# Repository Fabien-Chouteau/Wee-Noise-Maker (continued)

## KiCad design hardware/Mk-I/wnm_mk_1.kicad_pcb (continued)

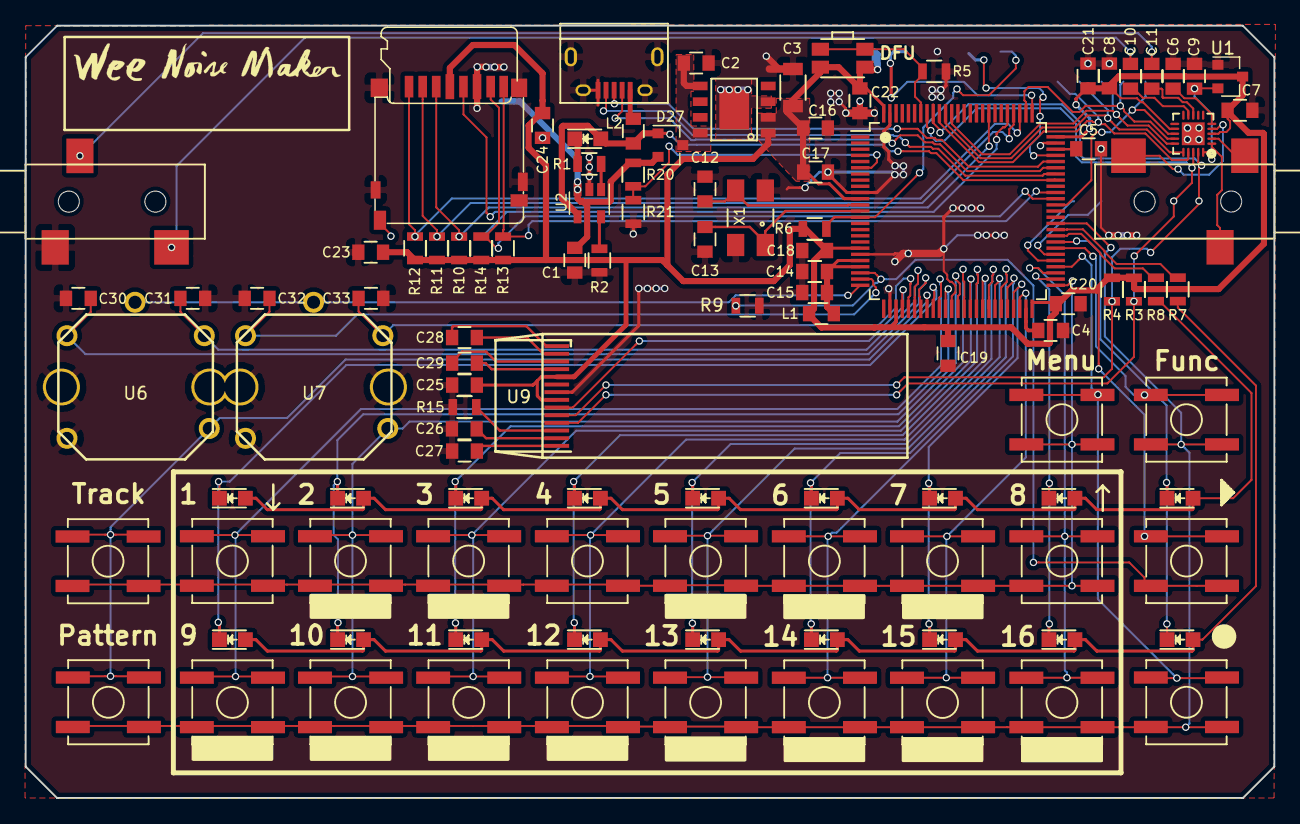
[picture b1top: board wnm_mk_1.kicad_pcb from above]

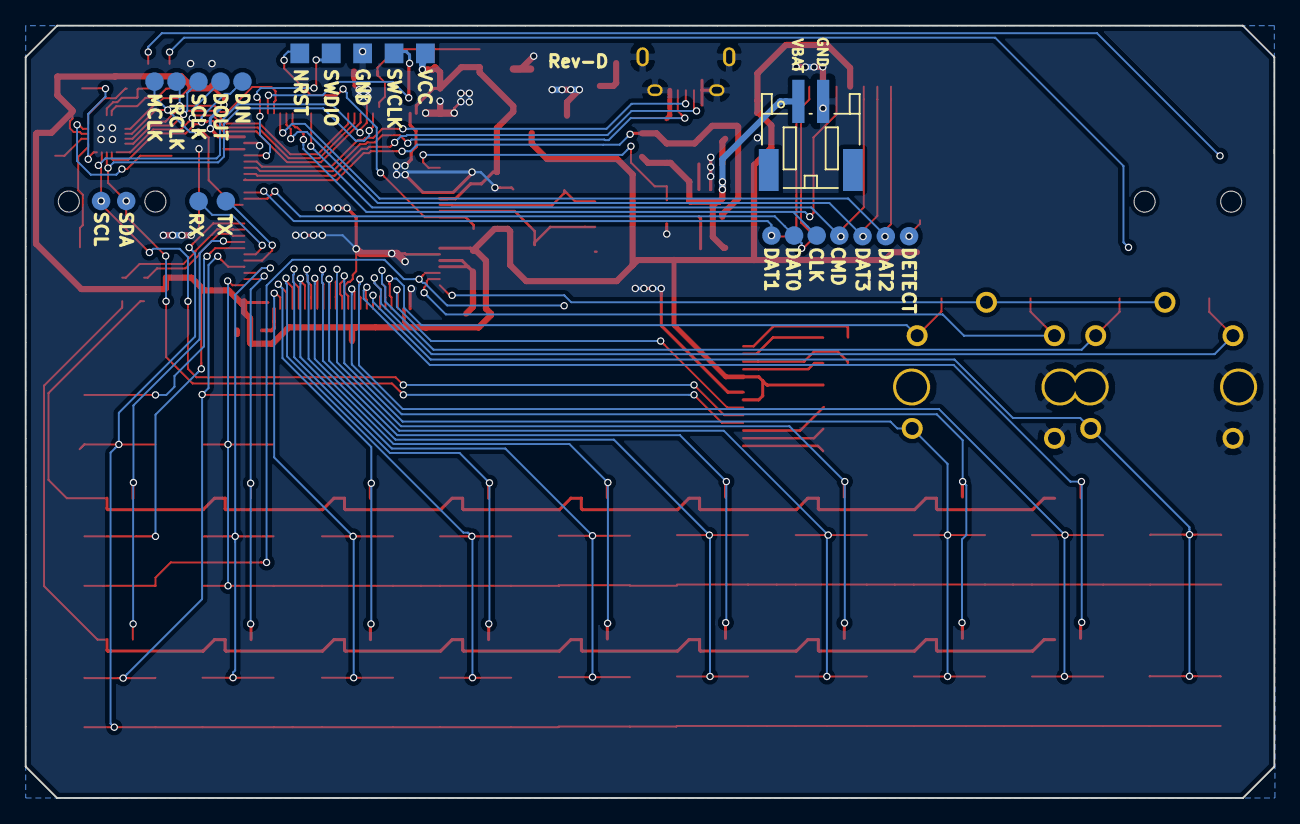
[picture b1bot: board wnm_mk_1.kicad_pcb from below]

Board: 2 copper layers, 100.9 x 62.4 mm, 126 parts (18 on the bottom side), 87 nets.

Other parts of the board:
TP_CMD1: TEST; Measurement_Point_Round-SMD-Pad_Small
TP_DAT2, TP_DAT3: TEST; Measurement_Point_Round-SMD-Pad_Small

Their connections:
SD_CMD: TP_CMD1.1; also elsewhere on the board
SD_DAT2: TP_DAT2.1; also elsewhere on the board
SD_DAT3: TP_DAT3.1; also elsewhere on the board

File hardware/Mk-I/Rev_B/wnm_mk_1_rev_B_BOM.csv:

Id,Designator,Package,Quantity,Designation,Supplier and ref,link
1,G***,logo_hand_line,1,LOGO,,
2,G***,logo_hand_text,1,LOGO,,
3,C2,C_0805,1,4.7uF,08053D475KAT2A,http://www.mouser.fr/ProductDetail/AVX/08053D475KAT2A/?qs=sG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
4,U4,LQFP-100_14x14mm_Pitch0.5mm,1,STM32F407VG,STM32F427VIT6,http://www.mouser.fr/ProductDetail/STMicroelectronics/STM32F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
5,"C26,C27,C1,C25",C_0805,4,10uF,08053D106KAT2A,http://www.mouser.fr/ProductDetail/AVX/08053D106KAT2A/?qs=sG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
6,BT1,PINHEAD1-2,1,BATTERY,,
7,"D24,D25,D1,D2,D3,D4,D5,D6,D7,D8,D9,D10,D11,D12,D13,D14,D15,D16,D17,D18,D20,D21,D22,D23,BAT1",LED_0805,25,LED,150080RS75000,http://www.mouser.fr/Search/ProductDetail.aspx?R=150080RS750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
8,"SW4,SW1,SW7,SW8,SW2,SW3,SW5,SW6,SW9,SW10,SW11,SW12,SW13,SW14,SW15,SW16,Play1,Write1,Play2,SW18,SW19,SW20,SW21,SW22",SW_SPST_B3SL-1002P,24,SW_PUSH,,
9,"C6,C7,C8,C9,C15,C17,C18,C19,C20,C21,C22,C23,C30,C31,C32,C33",C_0805,16,0.1uF,08053C104KAT2A,http://www.mouser.fr/ProductDetail/AVX/08053C104KAT2A/?qs=sG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
10,R1,R_0805,1,1K,CRCW08051K00JNEA,http://www.mouser.fr/ProductDetail/Vishay/CRCW08051K00JNEA/?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
11,U2,SOT-23-5,1,MCP73831,MCP73831T-2ACI/OT,http://www.mouser.fr/ProductDetail/Microchip-Technology/MCP7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
12,CON1,USB_Micro-B,1,USB-MICRO-B,,
13,C3,C_1206,1,47uF,C3216X5R1C476M160AB,http://www.mouser.fr/ProductDetail/TDK/C3216X5R1C476M160AB/?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
14,"R2,R3,R4,R5,R6,R10,R11,R12,R13,R14,R20,R21",R_0805,12,10K,CRCW080510K0JNEA,http://www.mouser.fr/ProductDetail/Vishay/CRCW080510K0JNEA
15,D27,SOT-23,1,DOUBLE_SCH_KCOM_PMEG2005CT,,
16,"C4,C5",C_0805,2,2.2uF,0805YC225KAT2A,http://www.mouser.fr/ProductDetail/AVX/0805YC225KAT2A/?qs=sG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
17,"C10,C11,C14,C28,C29",C_0805,5,1uF,08053C105KAT2A,http://www.mouser.fr/ProductDetail/AVX/08053C105KAT2A/?qs=sG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
18,U5,UQFN-20-1EP_3x3mm_Pitch0.4mm,1,SGTL5000,SGTL5000XNAA3R2,http://www.mouser.fr/ProductDetail/NXP-Freescale/SGTL5000XNA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
19,"C12,C13",C_0805,2,20pF,0805YA200KAT2A,http://www.mouser.fr/ProductDetail/AVX/0805YA200KAT2A/?qs=qV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
20,"C16,C24",C_0805,2,22uF,GRM21BR61C226ME44L,http://www.mouser.fr/ProductDetail/Murata-Electronics/GRM21B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
21,"L1,L2",C_0805,2,15Ohm,CBC2012T4R7M,http://www.mouser.fr/ProductDetail/Taiyo-Yuden/CBC2012T4R7M/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
22,"R7,R8,R9",R_0805,3,330,CRCW0805330RJNEA,http://www.mouser.fr/ProductDetail/Vishay/CRCW0805330RJNEA/?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
23,R15,R_0805,1,68k,CRCW080568K0JNEA,http://www.mouser.fr/ProductDetail/Vishay/CRCW080568K0JNEA/?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
24,"R16,R17,R18,R19",R_0805,4,27K,CRCW080527K0JNEA,http://www.mouser.fr/ProductDetail/Vishay/CRCW080527K0JNEA/?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
25,X1,Crystal_HC49-U_Vertical,1,CRYSTAL,LFXTAL003156Bulk,http://www.mouser.fr/ProductDetail/IQD/LFXTAL003156Bulk/?qs=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
26,"HP_OUT1,LINE_IN1",lumberg_3.5_audio_jack_1503_02,2,3.5_audio_jack,,
27,U8,MOLEX_microSD_47219-2001,1,MOLEX_microSD_47219-2001,,
28,U9,MIDAS_MCOT096016AV_OLED,1,SSD1306,,
29,REF**,MountingHole_4.3mm_M4,1,MountingHole_4.3mm_M4,,
30,DFU_MODE1,SW_SPST_EVQP7A,1,Jumper_NO_Small,EVQ-P7A01P,http://www.mouser.fr/ProductDetail/Panasonic/EVQ-P7A01P/?qs=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
31,"U7,U6",encoder_EC12D,2,encoder_and_switch,EC12D1524403,http://www.mouser.fr/ProductDetail/ALPS/EC12D1524403/?qs=%2f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
32,U3,HTSOP-J8,1,BD33IA5,BD33IA5WEFJ-E2,http://www.mouser.fr/ProductDetail/ROHM-Semiconductor/BD33IA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
33,ext1,Socket_Strip_Straight_1x04,1,CONN_01X04,,
34,U10,STM32_SWD_Connector_SMD,1,STM32_SWD_Connector,,

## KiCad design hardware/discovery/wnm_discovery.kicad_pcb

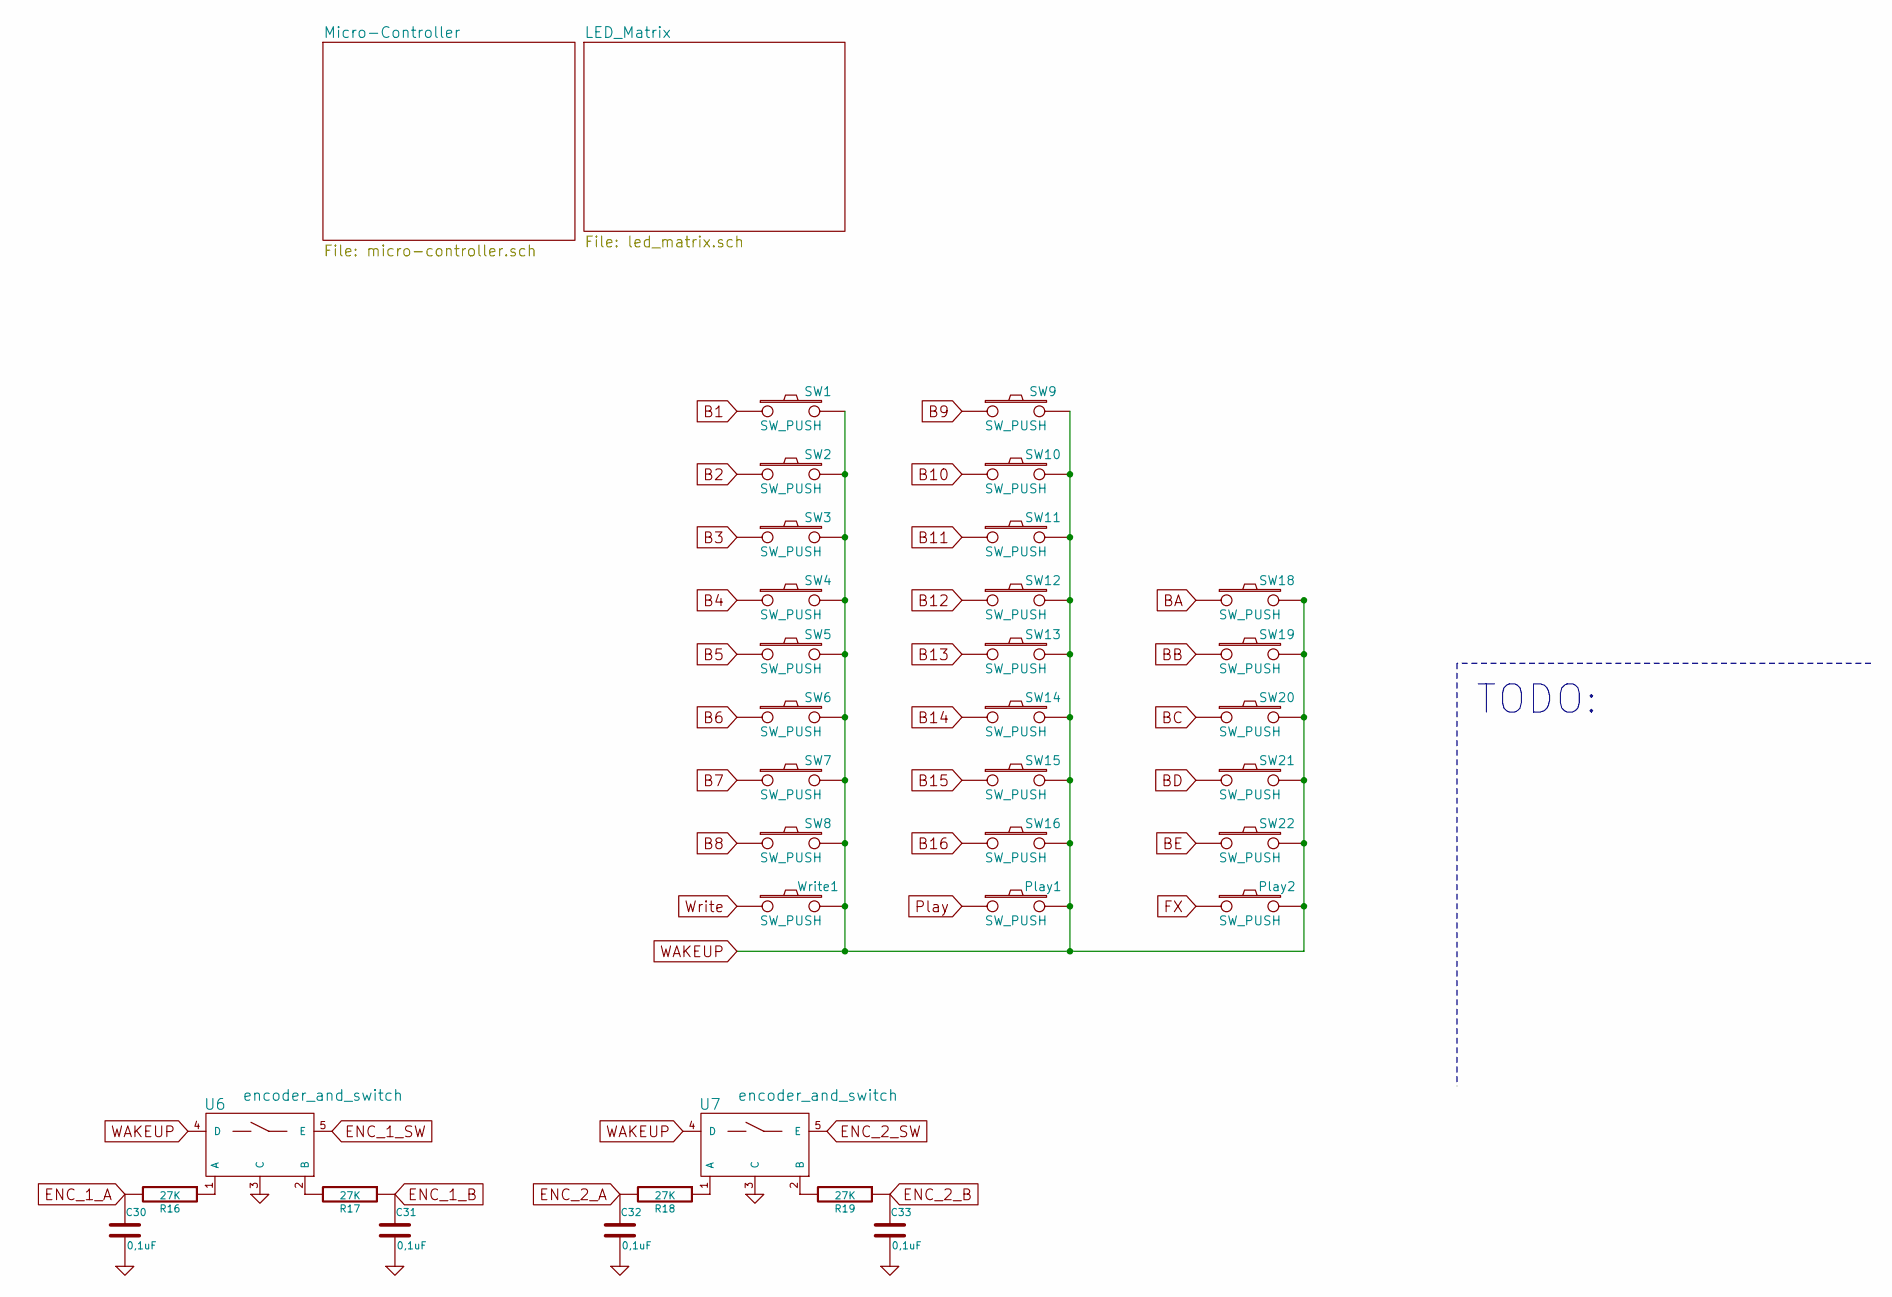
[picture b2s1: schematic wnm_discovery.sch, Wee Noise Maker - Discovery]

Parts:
C30, C31, C32, C33: 0,1uF; C_0805
Play1, Play2: SW_PUSH; SW_SPST_B3SL-1002P
R16, R17, R18, R19: 27K; R_0805
SW1, SW2, SW3, SW4, SW5, SW6, SW7, SW8, SW9, SW10, SW11, SW12, SW13, SW14, SW15, SW16, SW18, SW19, SW20, SW21, SW22: SW_PUSH; SW_SPST_B3SL-1002P
U6, U7: encoder_and_switch; encoder_EC12D
Write1: SW_PUSH; SW_SPST_B3SL-1002P

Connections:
B1: SW1.1; also elsewhere on the board
B2: SW2.1; also elsewhere on the board
B3: SW3.1; also elsewhere on the board
B4: SW4.1; also elsewhere on the board
B5: SW5.1; also elsewhere on the board
B6: SW6.1; also elsewhere on the board
B7: SW7.1; also elsewhere on the board
B8: SW8.1; also elsewhere on the board
B9: SW9.1; also elsewhere on the board
B10: SW10.1; also elsewhere on the board
B11: SW11.1; also elsewhere on the board
B12: SW12.1; also elsewhere on the board
B13: SW13.1; also elsewhere on the board
B14: SW14.1; also elsewhere on the board
B15: SW15.1; also elsewhere on the board
B16: SW16.1; also elsewhere on the board
BA: SW18.1; also elsewhere on the board
BB: SW19.1; also elsewhere on the board
BC: SW20.1; also elsewhere on the board
BD: SW21.1; also elsewhere on the board
BE: SW22.1; also elsewhere on the board
ENC_1_A: C30.1, R16.2; also elsewhere on the board
ENC_1_B: C31.1, R17.1; also elsewhere on the board
ENC_1_SW: U6.5 (E); also elsewhere on the board
ENC_2_A: C32.1, R18.2; also elsewhere on the board
ENC_2_B: C33.1, R19.1; also elsewhere on the board
ENC_2_SW: U7.5 (E); also elsewhere on the board
FX: Play2.1; also elsewhere on the board
GND: C30.2, C31.2, C32.2, C33.2, U6.3 (C), U7.3 (C); also elsewhere on the board
unnamed: R16.1, U6.1 (A)
unnamed: R17.2, U6.2 (B)
unnamed: R18.1, U7.1 (A)
unnamed: R19.2, U7.2 (B)
Play: Play1.1; also elsewhere on the board
WAKEUP: Play1.2, Play2.2, SW1.2, SW2.2, SW3.2, SW4.2, SW5.2, SW6.2, SW7.2, SW8.2, SW9.2, SW10.2, SW11.2, SW12.2, SW13.2, SW14.2, SW15.2, SW16.2, SW18.2, SW19.2, SW20.2, SW21.2, SW22.2, U6.4 (D), U7.4 (D), Write1.2; also elsewhere on the board
Write: Write1.1; also elsewhere on the board

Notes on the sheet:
TODO:

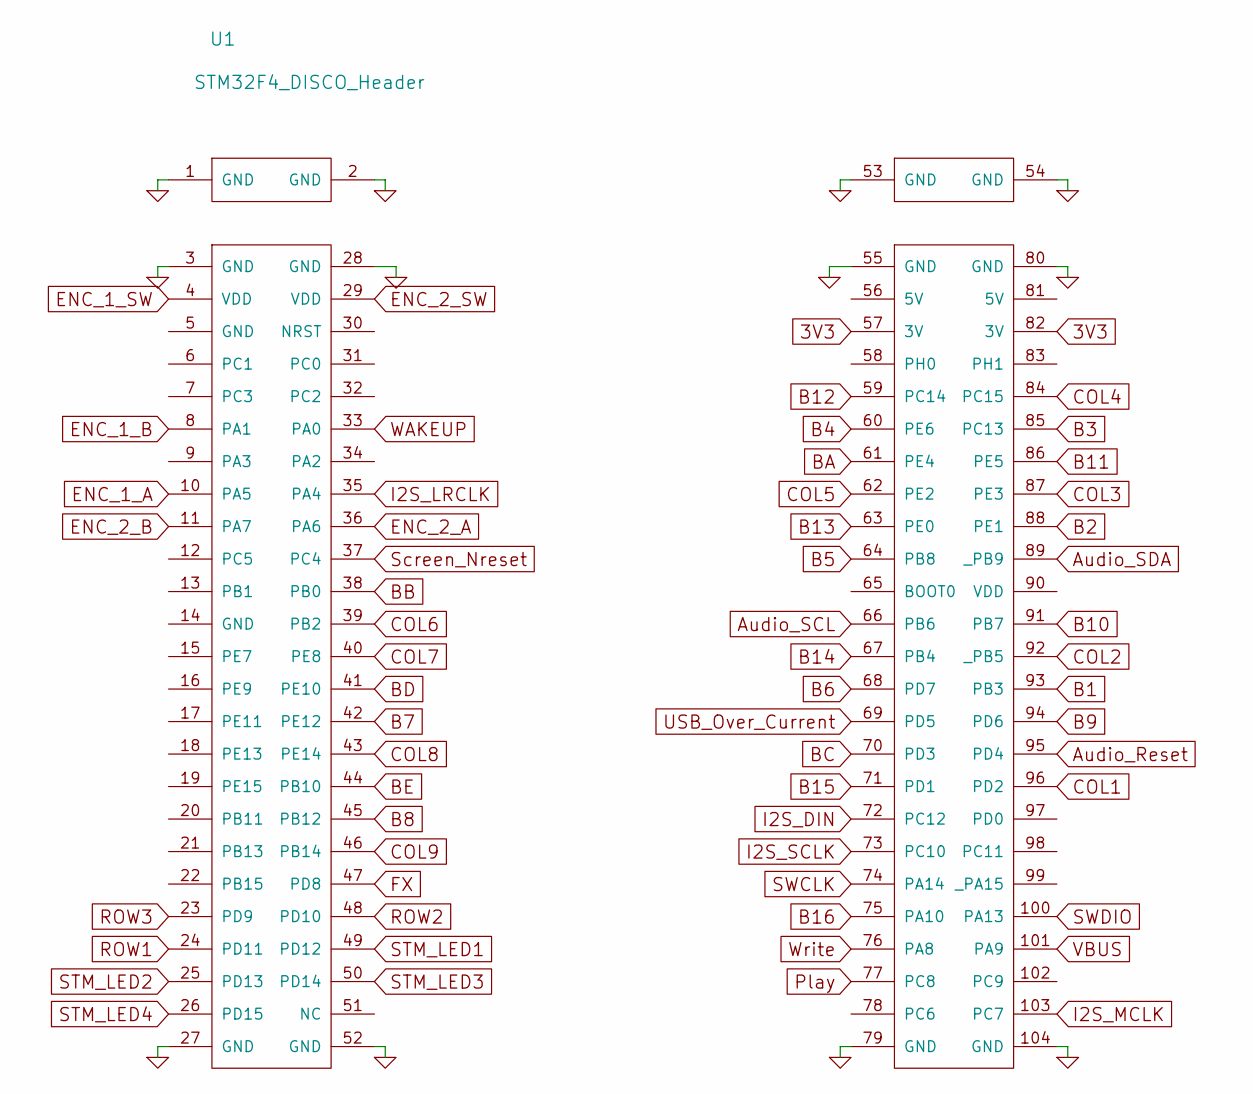
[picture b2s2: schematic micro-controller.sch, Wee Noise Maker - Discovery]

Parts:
U1: STM32F4_DISCO_Header; STM32F4-DISCO-HEADERS-TH

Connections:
3V3: U1.57 (3V), U1.82 (3V); also elsewhere on the board
Audio_Reset: U1.95 (PD4)
Audio_SCL: U1.66 (PB6); also elsewhere on the board
Audio_SDA: U1.89 (_PB9); also elsewhere on the board
B1: U1.93 (PB3); also elsewhere on the board
B2: U1.88 (PE1); also elsewhere on the board
B3: U1.85 (PC13); also elsewhere on the board
B4: U1.60 (PE6); also elsewhere on the board
B5: U1.64 (PB8); also elsewhere on the board
B6: U1.68 (PD7); also elsewhere on the board
B7: U1.42 (PE12); also elsewhere on the board
B8: U1.45 (PB12); also elsewhere on the board
B9: U1.94 (PD6); also elsewhere on the board
B10: U1.91 (PB7); also elsewhere on the board
B11: U1.86 (PE5); also elsewhere on the board
B12: U1.59 (PC14); also elsewhere on the board
B13: U1.63 (PE0); also elsewhere on the board
B14: U1.67 (PB4); also elsewhere on the board
B15: U1.71 (PD1); also elsewhere on the board
B16: U1.75 (PA10); also elsewhere on the board
BA: U1.61 (PE4); also elsewhere on the board
BB: U1.38 (PB0); also elsewhere on the board
BC: U1.70 (PD3); also elsewhere on the board
BD: U1.41 (PE10); also elsewhere on the board
BE: U1.44 (PB10); also elsewhere on the board
COL1: U1.96 (PD2); also elsewhere on the board
COL2: U1.92 (_PB5); also elsewhere on the board
COL3: U1.87 (PE3); also elsewhere on the board
COL4: U1.84 (PC15); also elsewhere on the board
COL5: U1.62 (PE2); also elsewhere on the board
COL6: U1.39 (PB2); also elsewhere on the board
COL7: U1.40 (PE8); also elsewhere on the board
COL8: U1.43 (PE14); also elsewhere on the board
COL9: U1.46 (PB14); also elsewhere on the board
ENC_1_A: U1.10 (PA5); also elsewhere on the board
ENC_1_B: U1.8 (PA1); also elsewhere on the board
ENC_1_SW: U1.4 (VDD); also elsewhere on the board
ENC_2_A: U1.36 (PA6); also elsewhere on the board
ENC_2_B: U1.11 (PA7); also elsewhere on the board
ENC_2_SW: U1.29 (VDD); also elsewhere on the board
FX: U1.47 (PD8); also elsewhere on the board
GND: U1.1 (GND), U1.2 (GND), U1.3 (GND), U1.27 (GND), U1.28 (GND), U1.52 (GND), U1.53 (GND), U1.54 (GND), U1.55 (GND), U1.79 (GND), U1.80 (GND), U1.104 (GND); also elsewhere on the board
I2S_DIN: U1.72 (PC12)
I2S_LRCLK: U1.35 (PA4)
I2S_MCLK: U1.103 (PC7)
I2S_SCLK: U1.73 (PC10)
Play: U1.77 (PC8); also elsewhere on the board
ROW1: U1.24 (PD11); also elsewhere on the board
ROW2: U1.48 (PD10); also elsewhere on the board
ROW3: U1.23 (PD9); also elsewhere on the board
STM_LED1: U1.49 (PD12)
STM_LED2: U1.25 (PD13)
STM_LED3: U1.50 (PD14)
STM_LED4: U1.26 (PD15)
SWCLK: U1.74 (PA14)
SWDIO: U1.100 (PA13)
Screen_NReset: U1.37 (PC4); also elsewhere on the board
USB_Over_Current: U1.69 (PD5)
VBUS: U1.101 (PA9)
WAKEUP: U1.33 (PA0); also elsewhere on the board
Write: U1.76 (PA8); also elsewhere on the board

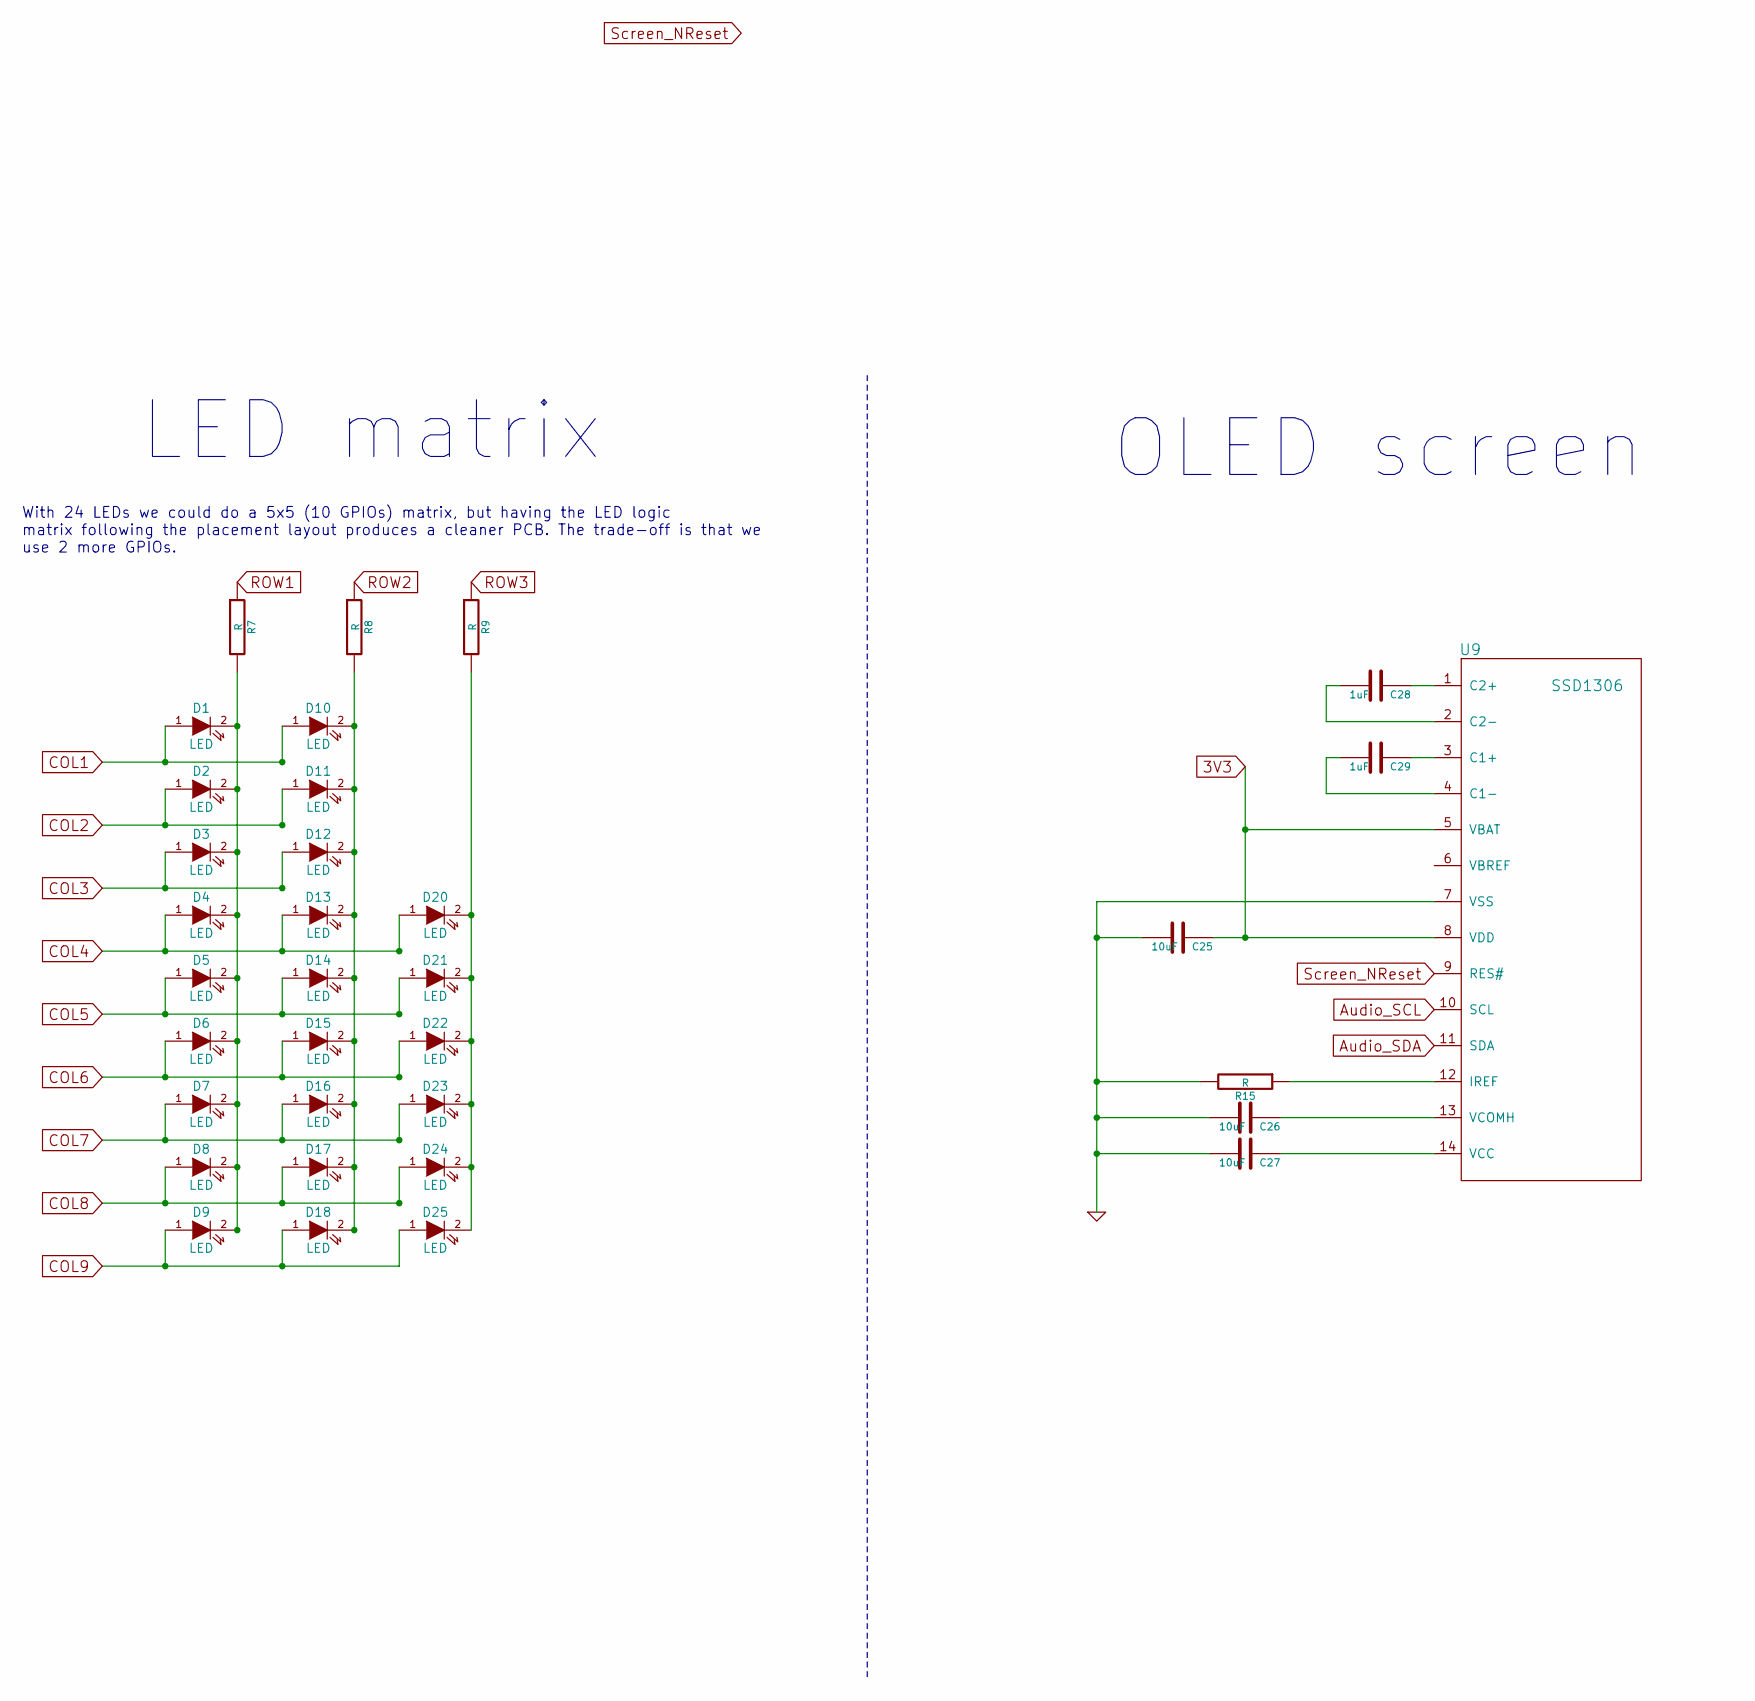
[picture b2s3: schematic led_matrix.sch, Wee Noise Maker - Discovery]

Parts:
C25, C26, C27: 10uF; C_0805
C28, C29: 1uF; C_0805
D1, D2, D3, D4, D5, D6, D7, D8, D9, D10, D11, D12, D13, D14, D15, D16, D17, D18, D20, D21, D22, D23, D24, D25: LED; LED_0805
R7, R8, R9, R15: R; R_0805
U9: SSD1306; MIDAS_MCOT096016AV_OLED

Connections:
3V3: C25.1, U9.5 (VBAT), U9.8 (VDD); also elsewhere on the board
Audio_SCL: U9.10 (SCL); also elsewhere on the board
Audio_SDA: U9.11 (SDA); also elsewhere on the board
COL1: D1.1 (A), D10.1 (A); also elsewhere on the board
COL2: D2.1 (A), D11.1 (A); also elsewhere on the board
COL3: D3.1 (A), D12.1 (A); also elsewhere on the board
COL4: D4.1 (A), D13.1 (A), D20.1 (A); also elsewhere on the board
COL5: D5.1 (A), D14.1 (A), D21.1 (A); also elsewhere on the board
COL6: D6.1 (A), D15.1 (A), D22.1 (A); also elsewhere on the board
COL7: D7.1 (A), D16.1 (A), D23.1 (A); also elsewhere on the board
COL8: D8.1 (A), D17.1 (A), D24.1 (A); also elsewhere on the board
COL9: D9.1 (A), D18.1 (A), D25.1 (A); also elsewhere on the board
GND: C25.2, C26.2, C27.2, R15.2, U9.7 (VSS); also elsewhere on the board
unnamed: C26.1, U9.13 (VCOMH)
unnamed: C27.1, U9.14 (VCC)
unnamed: C28.1, U9.1 (C2+)
unnamed: C28.2, U9.2 (C2-)
unnamed: C29.1, U9.3 (C1+)
unnamed: C29.2, U9.4 (C1-)
unnamed: D1.2 (K), D2.2 (K), D3.2 (K), D4.2 (K), D5.2 (K), D6.2 (K), D7.2 (K), D8.2 (K), D9.2 (K), R7.2
unnamed: D10.2 (K), D11.2 (K), D12.2 (K), D13.2 (K), D14.2 (K), D15.2 (K), D16.2 (K), D17.2 (K), D18.2 (K), R8.2
unnamed: D20.2 (K), D21.2 (K), D22.2 (K), D23.2 (K), D24.2 (K), D25.2 (K), R9.2
unnamed: R15.1, U9.12 (IREF)
ROW1: R7.1; also elsewhere on the board
ROW2: R8.1; also elsewhere on the board
ROW3: R9.1; also elsewhere on the board
Screen_NReset: U9.9 (RES#); also elsewhere on the board

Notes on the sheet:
With 24 LEDs we could do a 5x5 (10 GPIOs) matrix, but having the LED logic matrix following the placement layout produces a cleaner PCB. The trade-off is that we use 2 more GPIOs.
LED matrix
OLED screen

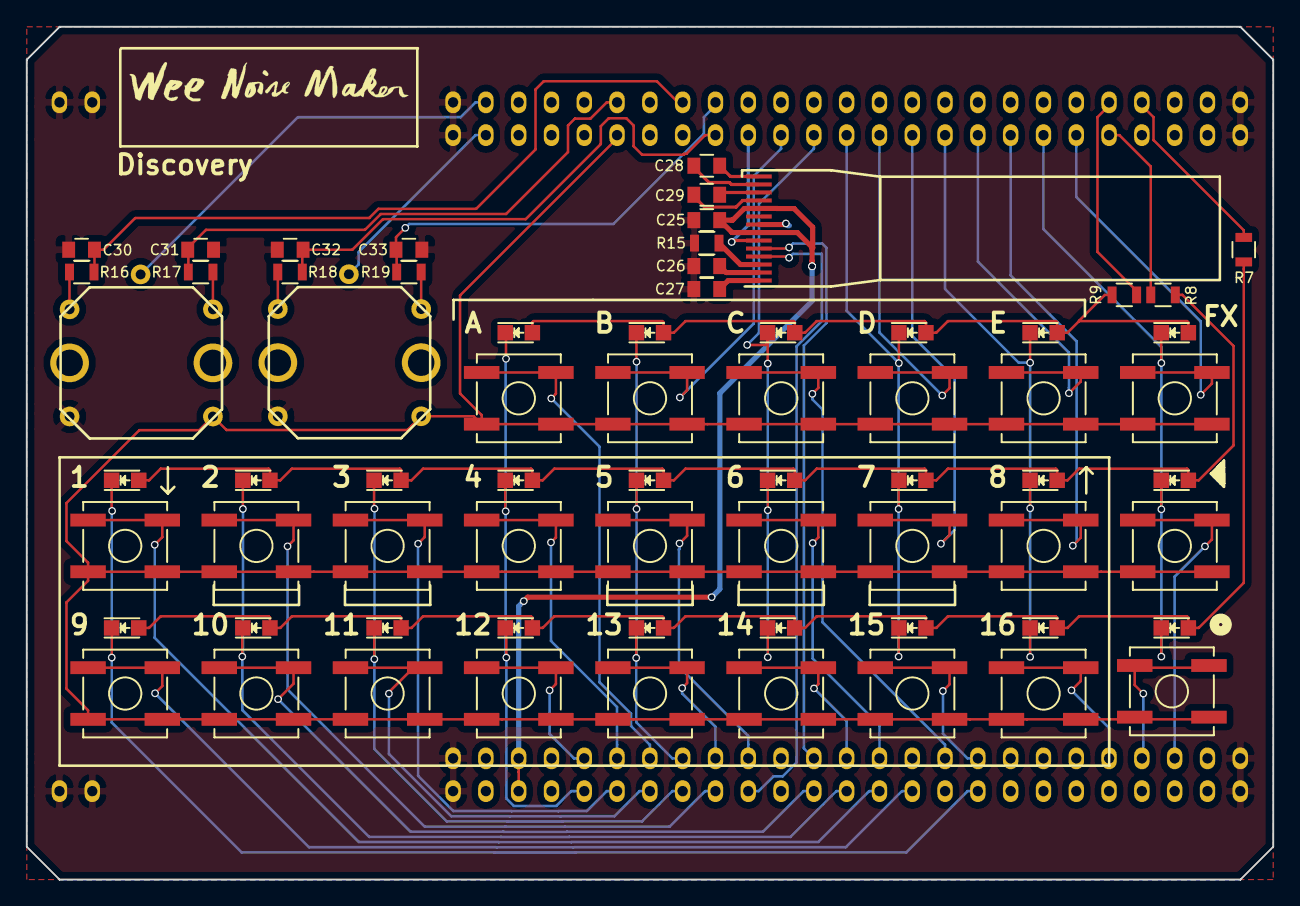
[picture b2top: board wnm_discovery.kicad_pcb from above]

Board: 2 copper layers, 96.5 x 66.0 mm, 69 parts (1 on the bottom side), 62 nets.

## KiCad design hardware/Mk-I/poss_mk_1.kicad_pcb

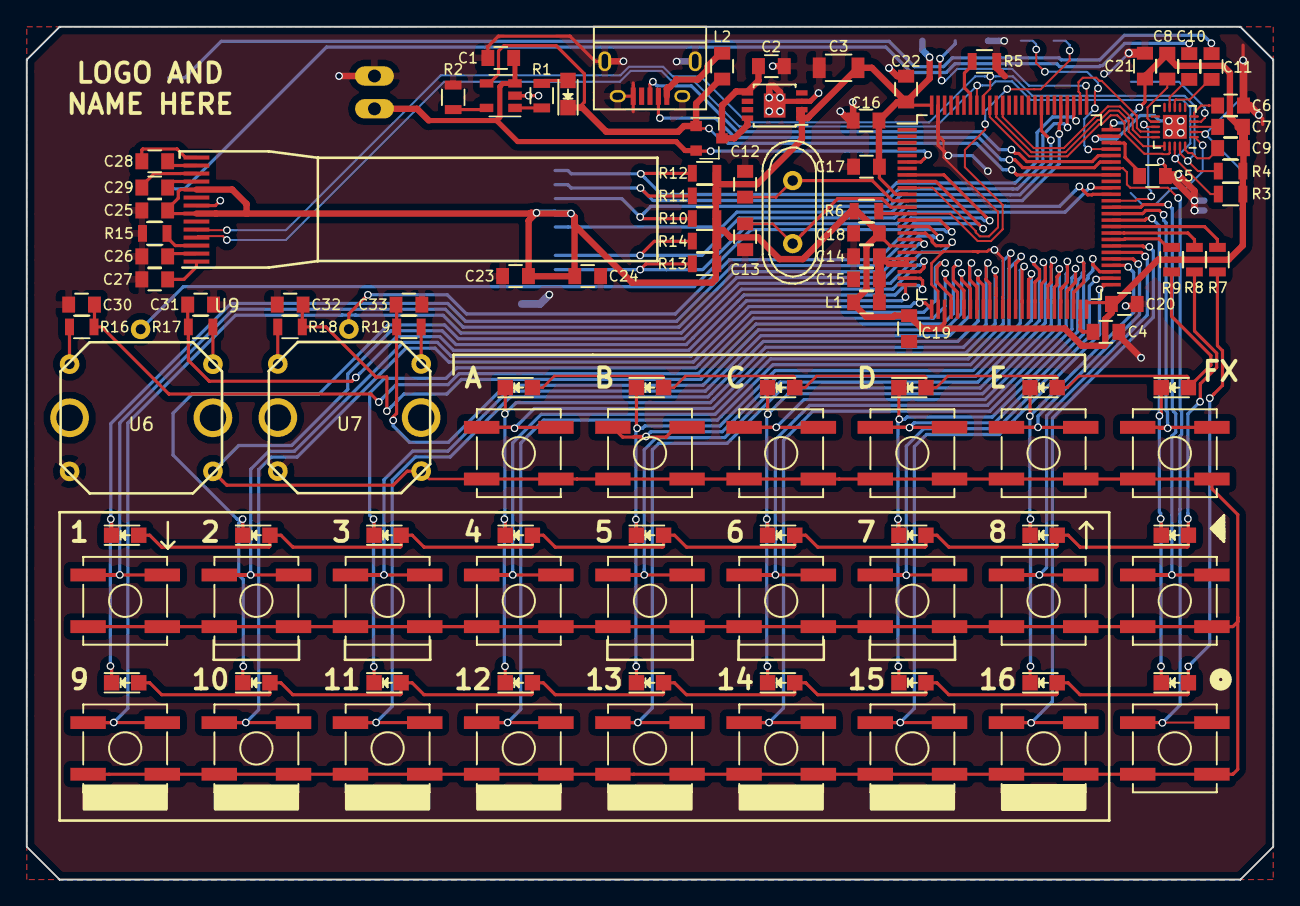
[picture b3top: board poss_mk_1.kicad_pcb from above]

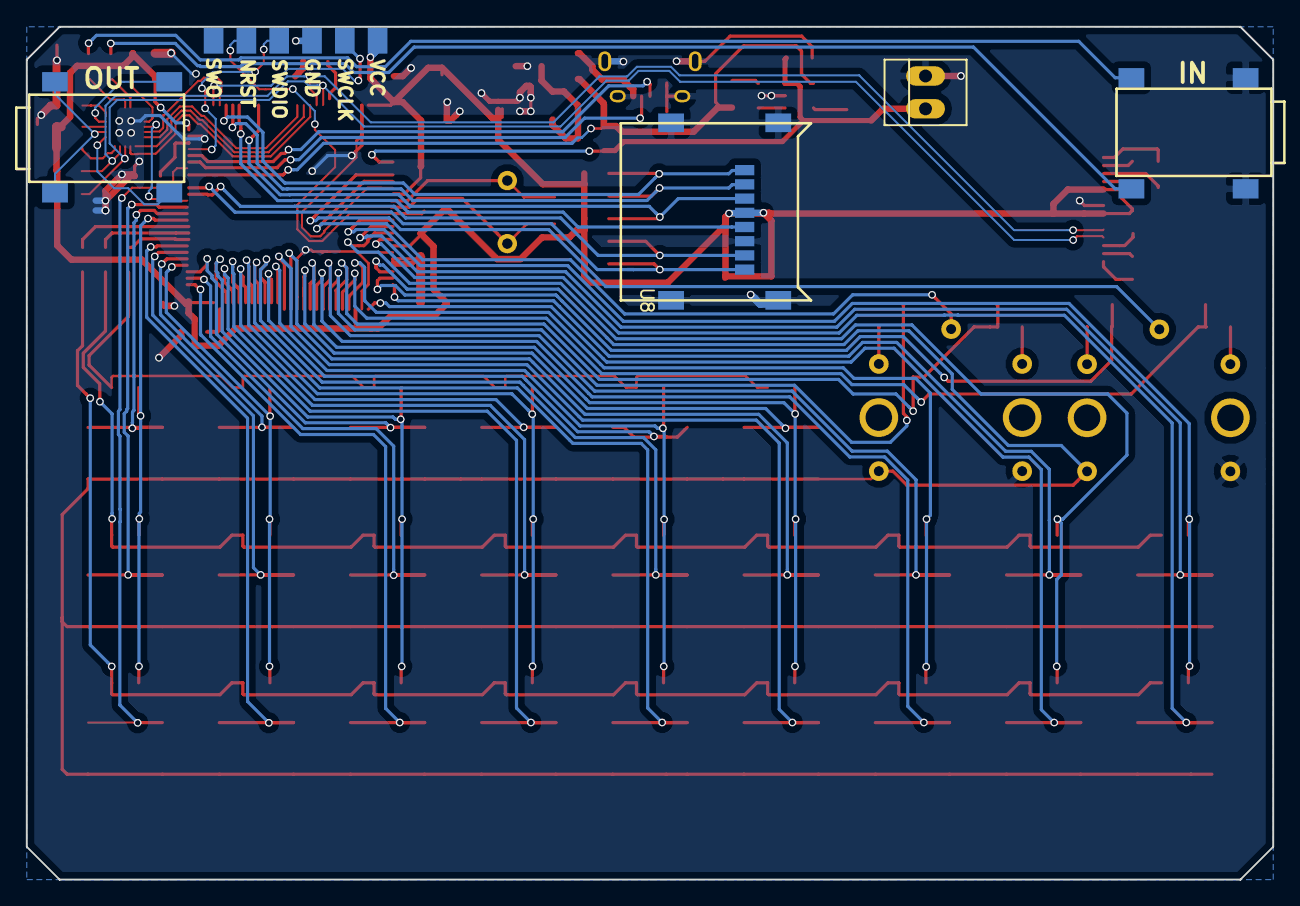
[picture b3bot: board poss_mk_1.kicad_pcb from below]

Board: 2 copper layers, 96.5 x 66.0 mm, 118 parts (5 on the bottom side), 101 nets.

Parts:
BAT1: LED; LED_0805
BT1: BATTERY; PINHEAD1-2
C1, C25, C26, C27: 10uF; C_0805
C2: 4.7uF; C_0805
C3: 47uF; C_1206
C4, C5: 2.2uF; C_0805
C6, C7, C8, C9, C15, C17, C18, C19, C20, C21, C22, C23: 0.1uF; C_0805
C10, C11, C14, C28, C29: 1uF; C_0805
C12, C13: C; C_0805
C16, C24: 22uF; C_0805
C30, C31, C32, C33: 0,1uF; C_0805
CON1: USB-MICRO-B; USB_Micro-B
D1, D2, D3, D4, D5, D6, D7, D8, D9, D10, D11, D12, D13, D14, D15, D16, D17, D18, D20, D21, D22, D23, D24, D25: LED; LED_0805
D27: DOUBLE_SCH_KCOM_PMEG2005CT; SOT-23
HP_OUT1: 3.5_audio_jack; lumberg_3.5_audio_jack_1503_02
L1, L2: 15Ohm; C_0805
LINE_IN1: 3.5_audio_jack; lumberg_3.5_audio_jack_1503_02
Play1, Play2: SW_PUSH; SW_SPST_B3SL-1002P
R1: 1K; R_0805
R2, R3, R4, R5, R6, R10, R11, R12, R13, R14: 10K; R_0805
R7, R8, R9, R15: R; R_0805
R16, R17, R18, R19: 27K; R_0805
SW1, SW2, SW3, SW4, SW5, SW6, SW7, SW8, SW9, SW10, SW11, SW12, SW13, SW14, SW15, SW16, SW18, SW19, SW20, SW21, SW22: SW_PUSH; SW_SPST_B3SL-1002P
U2: MCP73831; SOT-23-5
U3: BD33IA5; MSOP-8-1EP_3x3mm_Pitch0.65mm
U4: STM32F407VG; LQFP-100_14x14mm_Pitch0.5mm
U5: SGTL5000; UQFN-20-1EP_3x3mm_Pitch0.4mm
U6, U7: encoder_and_switch; encoder_EC12D
U8: MOLEX_microSD_47219-2001
U9: SSD1306; MIDAS_MCOT096016AV_OLED
U10: STM32_SWD_Connector; STM32_SWD_Connector_SMD
Write1: SW_PUSH; SW_SPST_B3SL-1002P
X1: CRYSTAL; Crystal_HC49-U_Vertical

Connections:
3V3: C3.1, C7.1, C8.1, C9.1, C16.2, C17.2, C18.2, C19.2, C20.2, C21.2, C22.2, C23.1, C24.1, C25.1, L1.1, R3.1, R4.1, R6.2, R10.1, R11.1, R12.1, R13.1, R14.1, U3.1, U3.2, U4.11, U4.19, U4.28, U4.50, U4.75, U4.100, U8.4, U9.5, U9.8, U10.1
Audio_SCL: R4.2, U4.92, U5.19, U9.10
Audio_SDA: R3.2, U4.93, U5.18, U9.11
B1: SW1.1, U4.16
B2: SW2.1, U4.25
B3: SW3.1, U4.33
B4: SW4.1, U4.38
B5: SW5.1, U4.42
B6: SW6.1, U4.46
B7: SW7.1, U4.52
B8: SW8.1, U4.56
B9: SW9.1, U4.18
B10: SW10.1, U4.26
B11: SW11.1, U4.34
B12: SW12.1, U4.39
B13: SW13.1, U4.43
B14: SW14.1, U4.47
B15: SW15.1, U4.51
B16: SW16.1, U4.57
BA: SW18.1, U4.36
BB: SW19.1, U4.41
BC: SW20.1, U4.45
BD: SW21.1, U4.53
BE: SW22.1, U4.55
COL1: D1.1, D10.1, U4.15
COL2: D2.1, D11.1, U4.17
COL3: D3.1, D12.1, U4.29
COL4: D4.1, D13.1, D20.1, U4.35
COL5: D5.1, D14.1, D21.1, U4.40
COL6: D6.1, D15.1, D22.1, U4.44
COL7: D7.1, D16.1, D23.1, U4.48
COL8: D8.1, D17.1, D24.1, U4.54
COL9: D9.1, D18.1, D25.1, U4.61
ENC_1_A: C30.1, R16.2, U4.30
ENC_1_B: C31.1, R17.1, U4.24
ENC_1_SW: U4.8, U6.5
ENC_2_A: C32.1, R18.2, U4.31
ENC_2_B: C33.1, R19.1, U4.32
ENC_2_SW: U4.9, U7.5
FS_DM: CON1.2, U4.70
FS_DP: CON1.3, U4.71
FX: Play2.1, U4.62
GND: BT1.2, C1.2, C2.2, C3.2, C4.2, C5.2, C6.2, C12.1, C13.1, C14.1, C15.1, C16.1, C17.1, C18.1, C19.1, C20.1, C21.1, C22.1, C23.2, C24.2, C25.2, C26.2, C27.2, C30.2, C31.2, C32.2, C33.2, CON1.5, CON1.6, LINE_IN1.2, R2.1, R5.2, R15.2, U2.2, U3.3, U3.9, U4.10, U4.20, U4.27, U4.37, U4.74, U4.99, U5.21, U6.3, U7.3, U8.6, U8.9, U9.7, U10.3
I2S_DIN: U4.91, U5.17
I2S_DOUT: U4.90, U5.16
I2S_LRCLK: U4.77, U5.14
I2S_MCLK: U4.64, U5.13
I2S_SCLK: U4.89, U5.15
NRST: R6.1, U4.14, U10.5
unnamed: BAT1.2, R1.2
unnamed: C4.1, U4.49
unnamed: C5.1, U4.73
unnamed: C6.1, U5.5
unnamed: C7.2, U5.3
unnamed: C8.2, U5.12
unnamed: C9.2, U5.20
unnamed: C10.1, LINE_IN1.1
unnamed: C10.2, U5.9
unnamed: C11.1, LINE_IN1.3
unnamed: C11.2, U5.8
unnamed: C12.2, U4.12, X1.1
unnamed: C13.2, U4.13, X1.2
unnamed: C14.2, C15.2, L1.2, U4.21, U4.22
unnamed: C26.1, U9.13
unnamed: C27.1, U9.14
unnamed: C28.1, U9.1
unnamed: C28.2, U9.2
unnamed: C29.1, U9.3
unnamed: C29.2, U9.4
unnamed: CON1.1, L2.2
unnamed: D1.2, D2.2, D3.2, D4.2, D5.2, D6.2, D7.2, D8.2, D9.2, R7.2
unnamed: D10.2, D11.2, D12.2, D13.2, D14.2, D15.2, D16.2, D17.2, D18.2, R8.2
unnamed: D20.2, D21.2, D22.2, D23.2, D24.2, D25.2, R9.2
unnamed: HP_OUT1.1, U5.4
unnamed: HP_OUT1.2, U5.2
unnamed: HP_OUT1.3, U5.1
unnamed: R1.1, U2.1
unnamed: R2.2, U2.5
unnamed: R5.1, U4.94
unnamed: R15.1, U9.12
unnamed: R16.1, U6.1
unnamed: R17.2, U6.2
unnamed: R18.1, U7.1
unnamed: R19.2, U7.2
Play: Play1.1, U4.63
ROW1: R7.1, U4.60
ROW2: R8.1, U4.59
ROW3: R9.1, U4.58
SD_CLK: U4.80, U8.5
SD_CMD: R10.2, U4.83, U8.3
SD_DAT0: R14.2, U4.65, U8.7
SD_DAT1: R13.2, U4.66, U8.8
SD_DAT2: R12.2, U4.78, U8.1
SD_DAT3: R11.2, U4.79, U8.2
SWCLK: U4.76, U10.2
SWDIO: U4.72, U10.4
VBAT: BT1.1, C1.1, D27.2, U2.3, U4.6
VBUS: BAT1.1, D27.1, L2.1, U2.4, U4.68
VIN: C2.1, D27.3, U3.5, U3.8
WAKEUP: Play1.2, Play2.2, SW1.2, SW2.2, SW3.2, SW4.2, SW5.2, SW6.2, SW7.2, SW8.2, SW9.2, SW10.2, SW11.2, SW12.2, SW13.2, SW14.2, SW15.2, SW16.2, SW18.2, SW19.2, SW20.2, SW21.2, SW22.2, U4.23, U6.4, U7.4, Write1.2
Write: U4.69, Write1.1
